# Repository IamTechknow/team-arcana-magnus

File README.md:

# team-arcana-magnus
This is the public repository for the Ingress Magnus 2018 Trickster Archetype Portal Luminenance Project. The portal name is known as Misty's Mind Palace. Currently, the status of the project is complete.

## Electronics Overview
The Trickster PLP had several components that utilized electronics (in increasing order of complexity), all of which contain code to operate: 

* The two player puzzle -  used two 16x32 LED Matrices and two buttons connected to a Raspberry Pi 3 and a 5V switched mode power supply.
* The passcode puzzle - used a monitor and three rotary encoders with 3D printed knobs attached
* The main lighting -  A DMXKing USB device that supported six PAR lights daisy-chained to a DMX universe with 25 meter DMX cables
* The Physical Glyph puzzle - custom electronics and a microcontroller. The EAGLE schematics to all of the custom electronics may be found here.

## Important Links
Check out our website at [http://mistysmindpalace.com](http://mistysmindpalace.com/) to find more information about our portal, such as the proposal, photos, and previous project updates.

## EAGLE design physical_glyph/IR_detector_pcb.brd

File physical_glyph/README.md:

# Physical Glyph (Final) Station

## Introduction
The Physical Glyph station allows the visitor to make use of all the information collected from the other puzzle stations. Glyphs must be entered in the correct order to solve this puzzle, upon doing so a prize is awarded. To input the glyphs, one must use a special wand shaped device and press a button to start the puzzle. From there on, the wand must be pointed to the glyph nodes which will light up LEDs indicating what the current glyph being entered looks like. Once all LEDs are lit up or the button is pressed the user may move on to the next glyph. 

In other words, hand gestures are used to draw glyphs, not finger swipes!

## Minimum Specification
* A disc will be laser cut with square holes to resemble glyph nodes
* The disc must be secured by the walls of the structure and there must be adequate space for all electronics
* Each hole will have its own infrared detector circuit
* Each IR detector circuit must support a range of 1-2 feet and only turn on when IR in a certain frequency is detected. It must not turn on by ambient lighting.
* Each circuit must provide a digital output for the microcontroller indicating IR is detected
* The microcontroller to use must support at least 24 GPIO pins, 22 for each set of IR circuit and a LED to indicate it has detected IR during a glyph, 1 for the wand button, and 1 for an actuator that releases the swag prize. Networking is not required.
* A wand device shall emit the IR at a certain frequency that is to be detected by any IR circuit. It is controlled by a button to allow the user to finish a glyph or start the puzzle. The button output must be debounced.
* When enough glyphs have been entered, the LEDs will light up to indicate whether the sequence of glyphs were correct or not. If they were, a check will be shown, and the actuator will turn to release a prize. Otherwise a cross is shown. The wand button when pressed will now start go to the initial screen.
* The microcontroller program must keep track of the glyphs recorded, and game states including initial idle, puzzle in session, and when the puzzle has ended.
* In the initial idle state the LEDs could show a hint for the Low Tech puzzle.

## Glyph order
| Glyph     |
| --------- |
| Search    |
| Answer    |
| Gain      |
| Unbounded |
| Knowledge |
| Idea      |

## Materials
* Wooden or card board to cut holes that resemble a glyph interface pattern.
* Microcontroller with lots of ports, either a PSoC 5LP or Arduino Mega 2560
* Fabricated PCBs, solder, solder paste, and an iron
* 22 and 24 gauge solid core wiring
* An actuator (servo or motor) and H-Bridge if motor is needed
* Push Button
* IR detection circuit materials:
   * Phototransistors
   * IR Emitter
   * LM339 Comparator
   * Op-Amps
   * Resistors
   * Capacitors
   * Voltage regulators
   * Diodes
   * LEDs

## Program Description
The program will be run by a PSoC 5LP development board, which contains enough interrupt perpherials for all of our IR detector inputs and a button. Digital outputs will be connected to LEDs. The IR detectors have an active low output, due to the use of an inverting Schmitt Trigger to snap the output to digital low or high.

The microcontroller program can transition through three states, the idle or default state, the game state, and an ending state. In the idle state the game is waiting to begin with a push of a button so the LEDs are off, and can also display a hint for the low tech puzzle hint. When the button is pressed, the game begins and will allow the user to input the first glyph by waving the wand to the LEDs, which are all lit up. When a IR detector input goes low, the LED will turn off so the user can tell what shape they are trying to draw. When the user is finished with that glyph, he or she will press the button again to start the next glyph. When the last glyph is drawn, the game will transition to the ending state where it will let the user know whether it has succeeded or failed, with a check or X glyph. 

To check if the drawn glyph is correct, we can define our own glyph definitions and check whether or not a drawn glyph is the same by putting all drawn nodes into a simple boolean array that can act as a set. This also means order will not matter here unlike in Ingress. All correct glyphs will have no more than 11 nodes to connect, so if a user draws a glyph with more than 11 glyphs it cannot be valid.

If possible we can try to record how long the button is pressed by using both rising and falling interrupts to be able to implement an undo function.

## AAR
An [AAR](https://docs.google.com/document/d/1Uy8Y4W4OLF-Iq5YLK9eRnNFhhYjXUx_bJ7s4a8xR_as/edit#) has been written detailing the bring up of this project component.

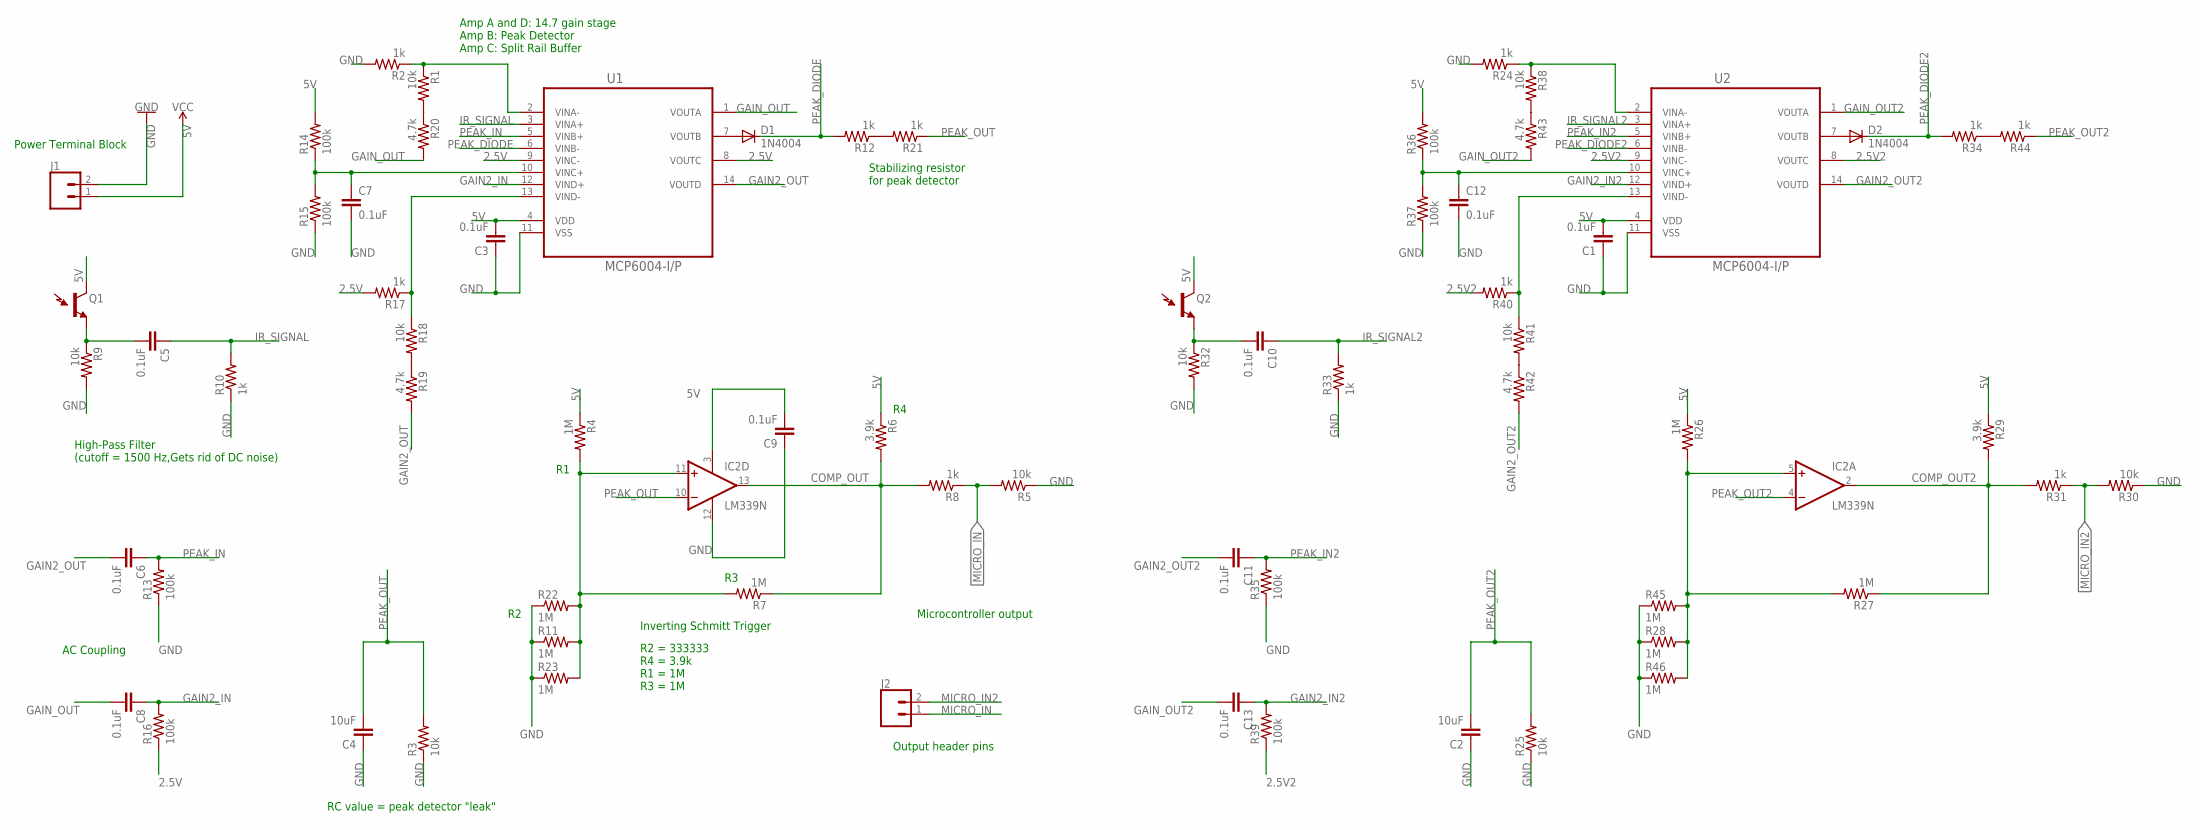
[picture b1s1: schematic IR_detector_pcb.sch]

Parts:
C1, C3, C5, C6, C7, C8, C9, C10, C11, C12, C13: 0.1uF; C025-024X044
C2, C4: 10uF; C025-024X044
D1, D2: 1N4004; DO41-10
IC2: LM339N; DIL14
J1: CONN_025MM; SCREWTERMINAL-5MM-2
J2: CONN_02; 1X02
Q1, Q2: LTR-301
R1, R3, R5, R9, R18, R25, R30, R32, R38, R41: 10k; 0204V
R2, R8, R10, R12, R17, R21, R24, R31, R33, R34, R40, R44: 1k; 0204V
R4, R7, R11, R22, R23, R26, R27, R28, R45, R46: 1M; 0204V
R6, R29: 3.9k; 0204V
R13, R14, R15, R16, R35, R36, R37, R39: 100k; 0204V
R19, R20, R42, R43: 4.7k; 0204V
U1, U2: MCP6004-I/P; DIP254P762X533-14

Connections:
2.5V: R16.1, R17.2, U1.8 (VOUTC), U1.9 (VINC-)
2.5V2: R39.1, R40.2, U2.8 (VOUTC), U2.9 (VINC-)
5V: C1.2, C3.2, C9.2, IC2.3 (V+), J1.1, Q1.C (C1), Q2.C (C1), R4.1, R6.1, R14.2, R26.1, R29.1, R36.2, U1.4 (VDD), U2.4 (VDD)
COMP_OUT: IC2.13 (OUT), R6.2, R7.1, R8.2
COMP_OUT2: IC2.2 (OUT), R27.1, R29.2, R31.2
GAIN2_IN: C8.1, R16.2, U1.12 (VIND+)
GAIN2_IN2: C13.1, R39.2, U2.12 (VIND+)
GAIN2_OUT: C6.2, R19.2, U1.14 (VOUTD)
GAIN2_OUT2: C11.2, R42.2, U2.14 (VOUTD)
GAIN_OUT: C8.2, R20.2, U1.1 (VOUTA)
GAIN_OUT2: C13.2, R43.2, U2.1 (VOUTA)
GND: C1.1, C2.1, C3.1, C4.1, C7.2, C9.1, C12.2, IC2.12 (GND), J1.2, R2.2, R3.1, R5.1, R9.2, R10.1, R11.1, R13.1, R15.1, R22.1, R23.1, R24.2, R25.1, R28.1, R30.1, R32.2, R33.1, R35.1, R37.1, R45.1, R46.1, U1.11 (VSS), U2.11 (VSS)
IR_SIGNAL: C5.1, R10.2, U1.3 (VINA+)
IR_SIGNAL2: C10.1, R33.2, U2.3 (VINA+)
MICRO_IN: J2.1, R5.2, R8.1
MICRO_IN2: J2.2, R30.2, R31.1
unnamed: C5.2, Q1.E (E1), R9.1
unnamed: D1.A, U1.7 (VOUTB)
unnamed: R17.1, R18.1, U1.13 (VIND-)
unnamed: C7.1, R14.1, R15.2, U1.10 (VINC+)
unnamed: R1.1, R2.1, U1.2 (VINA-)
unnamed: R18.2, R19.1
unnamed: R1.2, R20.1
unnamed: R12.1, R21.2
unnamed: IC2.5 (+IN), R26.2, R27.2, R28.2, R45.2, R46.2
unnamed: C10.2, Q2.E (E1), R32.1
unnamed: D2.A, U2.7 (VOUTB)
unnamed: C12.1, R36.1, R37.2, U2.10 (VINC+)
unnamed: R24.1, R38.1, U2.2 (VINA-)
unnamed: R40.1, R41.1, U2.13 (VIND-)
unnamed: R41.2, R42.1
unnamed: R38.2, R43.1
unnamed: R34.1, R44.2
unnamed: IC2.11 (+IN), R4.2, R7.2, R11.2, R22.2, R23.2
PEAK_DIODE: D1.C, R12.2, U1.6 (VINB-)
PEAK_DIODE2: D2.C, R34.2, U2.6 (VINB-)
PEAK_IN: C6.1, R13.2, U1.5 (VINB+)
PEAK_IN2: C11.1, R35.2, U2.5 (VINB+)
PEAK_OUT: C4.2, IC2.10 (-IN), R3.2, R21.1
PEAK_OUT2: C2.2, IC2.4 (-IN), R25.2, R44.1

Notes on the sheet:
Amp A and D: 14.7 gain stage Amp B: Peak Detector Amp C: Split Rail Buffer
R2 = 333333 R4 = 3.9k R1 = 1M R3 = 1M
RC value = peak detector "leak"
Inverting Schmitt Trigger
Microcontroller output
High-Pass Filter (cutoff = 1500 Hz,Gets rid of DC noise)
AC Coupling
Stabilizing resistor for peak detector
Power Terminal Block
Output header pins

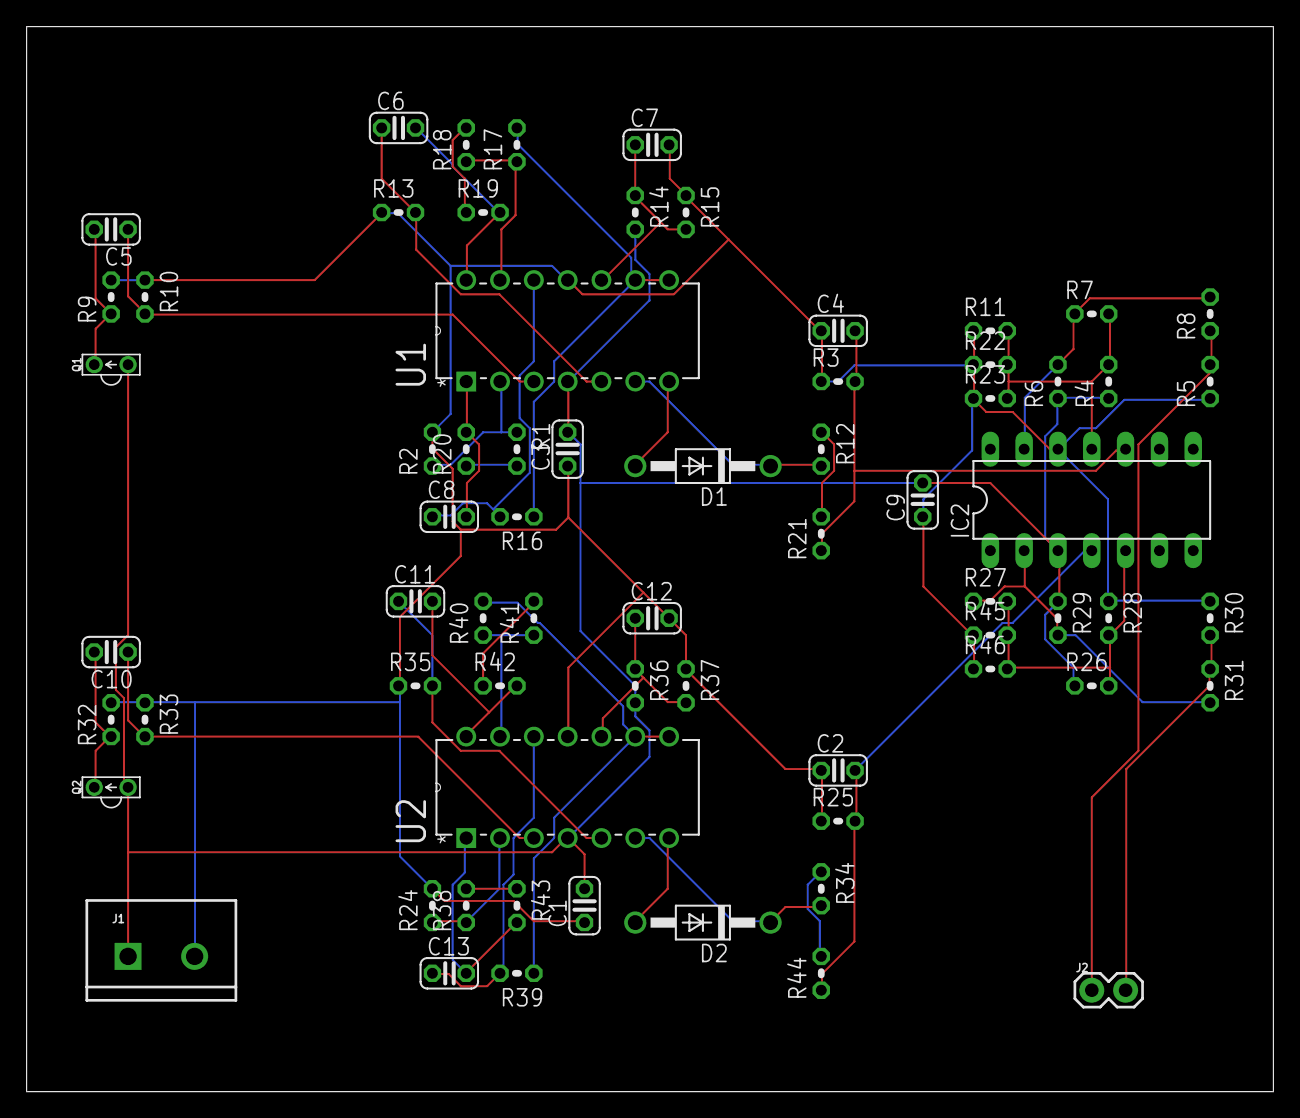
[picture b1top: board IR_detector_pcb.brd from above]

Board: 2 copper layers, 93.7 x 80.0 mm, 68 parts (0 on the bottom side), 40 nets.

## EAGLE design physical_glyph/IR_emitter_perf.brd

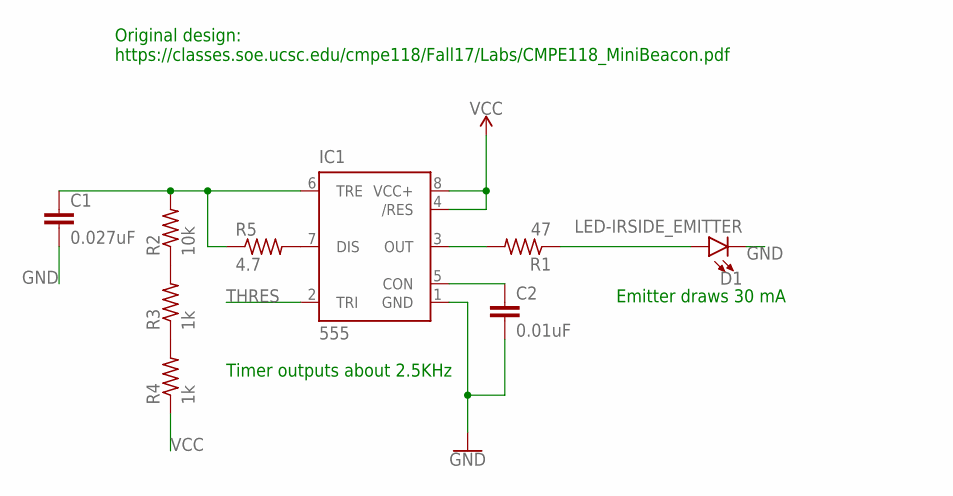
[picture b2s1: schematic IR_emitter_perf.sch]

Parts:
C1: 0.027uF; C025-024X044
C2: 0.01uF; C025-024X044
D1: LED-IRSIDE_EMITTER; LTE-302
IC1: 555; DIP08
R1: 47; 0204V
R2: 10k; 0204V
R3, R4: 1k; 0204V
R5: 4.7; 0204V

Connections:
GND: C1.2, C2.2, D1.C, IC1.1 (GND)
unnamed: IC1.3 (OUT), R1.2
unnamed: D1.A, R1.1
unnamed: C2.1, IC1.5 (CON)
unnamed: IC1.7 (DIS), R5.2
unnamed: R2.1, R3.2
unnamed: R3.1, R4.2
THRES: C1.1, IC1.2 (TRI), IC1.6 (TRE), R2.2, R5.1
VCC: IC1.4 (/RES), IC1.8 (VCC+), R4.1

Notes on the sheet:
Original design: https://classes.soe.ucsc.edu/cmpe118/Fall17/Labs/CMPE118_MiniBeacon.pdf
Emitter draws 30 mA
Timer outputs about 2.5KHz

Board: 2 copper layers, 9 parts (0 on the bottom side), 9 nets, no tracks yet.

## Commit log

2018-04-04 Add minimum specifications
2018-04-08 Add rough draft of IR detector circuit
2018-04-09 Fix inverted Schmitt Trigger
2018-04-09 Remove unneeded buffer
2018-04-09 Change gain stage and output
2018-04-10 Add rotary encoder test for RPi
2018-04-14 Change hystersis bounds and peak detector
2018-04-14 Add high-pass filter
2018-04-15 Add IR emitter circuit
2018-04-19 Add 2nd gain stage, split rail, and AC coupling
2018-04-19 Change hystersis upper limit to 2V
2018-04-20 Change gain resistors, fix net issue
2018-04-20 Add board file for detector
2018-04-24 Redo wire config to be the same as in the RPI LED matrix library
2018-04-24 Update low tech puzzle doc
2018-04-24 add submodule for LED matrix library
2018-04-25 Simplify all resistors and clarify comparator resistors
2018-04-26 Start on Flappy XM program, still need Makefile
2018-04-30 Update gitignore for PSOC
2018-04-30 Start Two player game code
2018-04-30 Start on PSOC project
2018-05-01 Add polling script
2018-05-01 Document current MQTT events
2018-05-01 WIP on Tecthulhu control django site
2018-05-02 Website initially works
2018-05-02 Add buttons, update bootstrap
2018-05-02 Final edits and fixes to IR detector circuit
2018-05-03 Add test to control DMX PAR lights
2018-05-03 Add script to control lighting based on MQTT events
2018-05-07 Work on Physical glyph readme and program
2018-05-08 WIP on physical glyph program part 2
2018-05-08 Change the ports to what they should be
2018-05-10 Physical glyph puzzle works with three detectors now
2018-05-12 Added tests for the buttons and MQTT
2018-05-13 Make two player game compliable
2018-05-13 Update PLP site to allow level 0 and to turn off lights
2018-05-14 Add messages on site, update matrix library
2018-05-14 Fixed messages and faction change buttons
2018-05-14 Fix tab errors
2018-05-14 Enable the last 3 IO pins, add remaining glyph info
2018-05-15 Added PCB design
2018-05-15 Udate after discussion with IamTechknow
2018-05-16 Fixed Rotazy Directions
2018-05-16 Added v0 of algo chooser
2018-05-17 Added ButtonEncoder
2018-05-17 Added Consts for Button1
2018-05-17 Added Management of selection by Button1 Click
2018-05-18 Add makefile for tests, work on two player game
2018-05-19 Added software debouncing on test
2018-05-20 Improve debouncing, game updates XM particle positions
2018-05-20 Lower brightness, add glyph info
2018-05-20 Isolated AlgorithmChooser to be used multiple time
2018-05-20 Updated AlogorithmChooser - Added two new instances of AlgorithmChooser
2018-05-20 Isolates Button management code
2018-05-20 Show glyphs when game is won, fix changes from last commit
2018-05-21 Added easier position configuration
2018-05-21 Added autonomise AlgoChooser
2018-05-21 Added Display od encoded value in Middle of cicrle
2018-05-21 Collision detection now working
2018-05-21 Particles blink upon collision
2018-05-21 Turn on MQTT integration
2018-05-22 Adjust the fading on the PAR lights
2018-05-22 Add glyph information
2018-05-22 Add script to connect with bluetooth speakers
2018-05-22 Portal control script can play sounds now
2018-05-22 Add IP address, turn on BT in script
2018-05-23 Update polling script
2018-05-24 Fixed a long standing regression with the IR circuit
2018-05-24 Add instructions to run django site
2018-05-26 Version 0.1
2018-05-26 Version 0.2
2018-05-26 Final commits for Physical Glyph program
2018-06-20 Add a test harness
2018-06-28 Fix wrong outpin pins, all pins are pull up now
2018-06-30 Add debouncer and improve button handling
2018-06-30 Add mapping from detectors to LED positions to turn on LEDs
2018-07-06 Update project documentation

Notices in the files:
parts and their libraries:
SparkFun-Sensors: Licensing: Creative Commons ShareAlike 4.0 International - https://creativecommons.org/licenses/by-sa/4.0
